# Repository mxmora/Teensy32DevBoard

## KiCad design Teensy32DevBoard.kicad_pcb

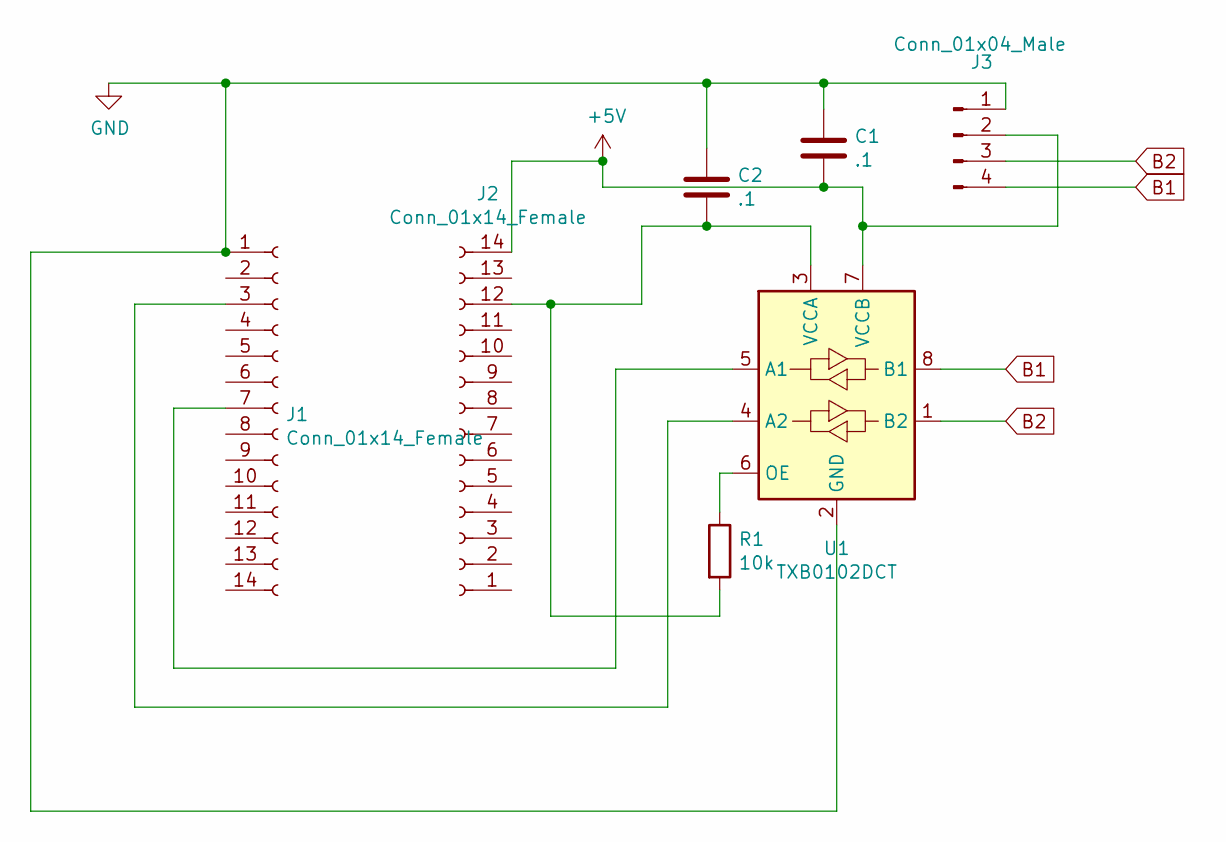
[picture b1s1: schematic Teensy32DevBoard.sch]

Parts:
C1, C2: .1; C_0402_1005Metric; LCSC C387958
J1, J2: Conn_01x14_Female; PinSocket_1x14_P2.54mm_Vertical
J3: Conn_01x04_Male; PinHeader_1x04_P2.54mm_Vertical
R1: 10k; R_0402_1005Metric
U1: TXB0102DCT; VSSOP-8_2.3x2mm_P0.5mm; LCSC C60709

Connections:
+5V: C1.2, J2.14, J3.2, U1.7 (VCCB)
B1: J3.4, U1.8 (B1)
B2: J3.3, U1.1 (B2)
GND: C1.1, C2.1, J1.1, J3.1, U1.2 (GND)
unnamed: C2.2, J2.12, R1.2, U1.3 (VCCA)
unnamed: J1.3, U1.4 (A2)
unnamed: J1.7, U1.5 (A1)
unnamed: R1.1, U1.6 (OE)

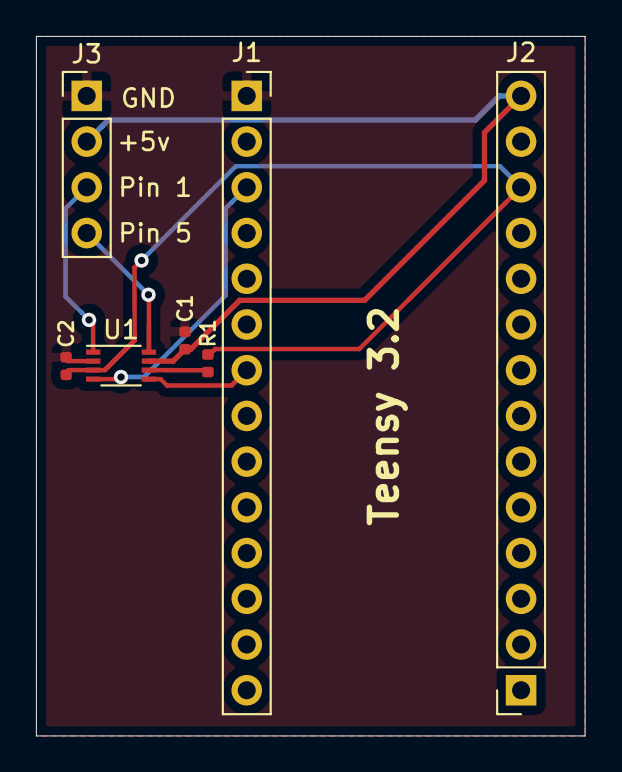
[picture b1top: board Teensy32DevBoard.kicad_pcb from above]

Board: 2 copper layers, 30.5 x 38.9 mm, 7 parts (0 on the bottom side), 8 nets.

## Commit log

2020-04-08 first check in
